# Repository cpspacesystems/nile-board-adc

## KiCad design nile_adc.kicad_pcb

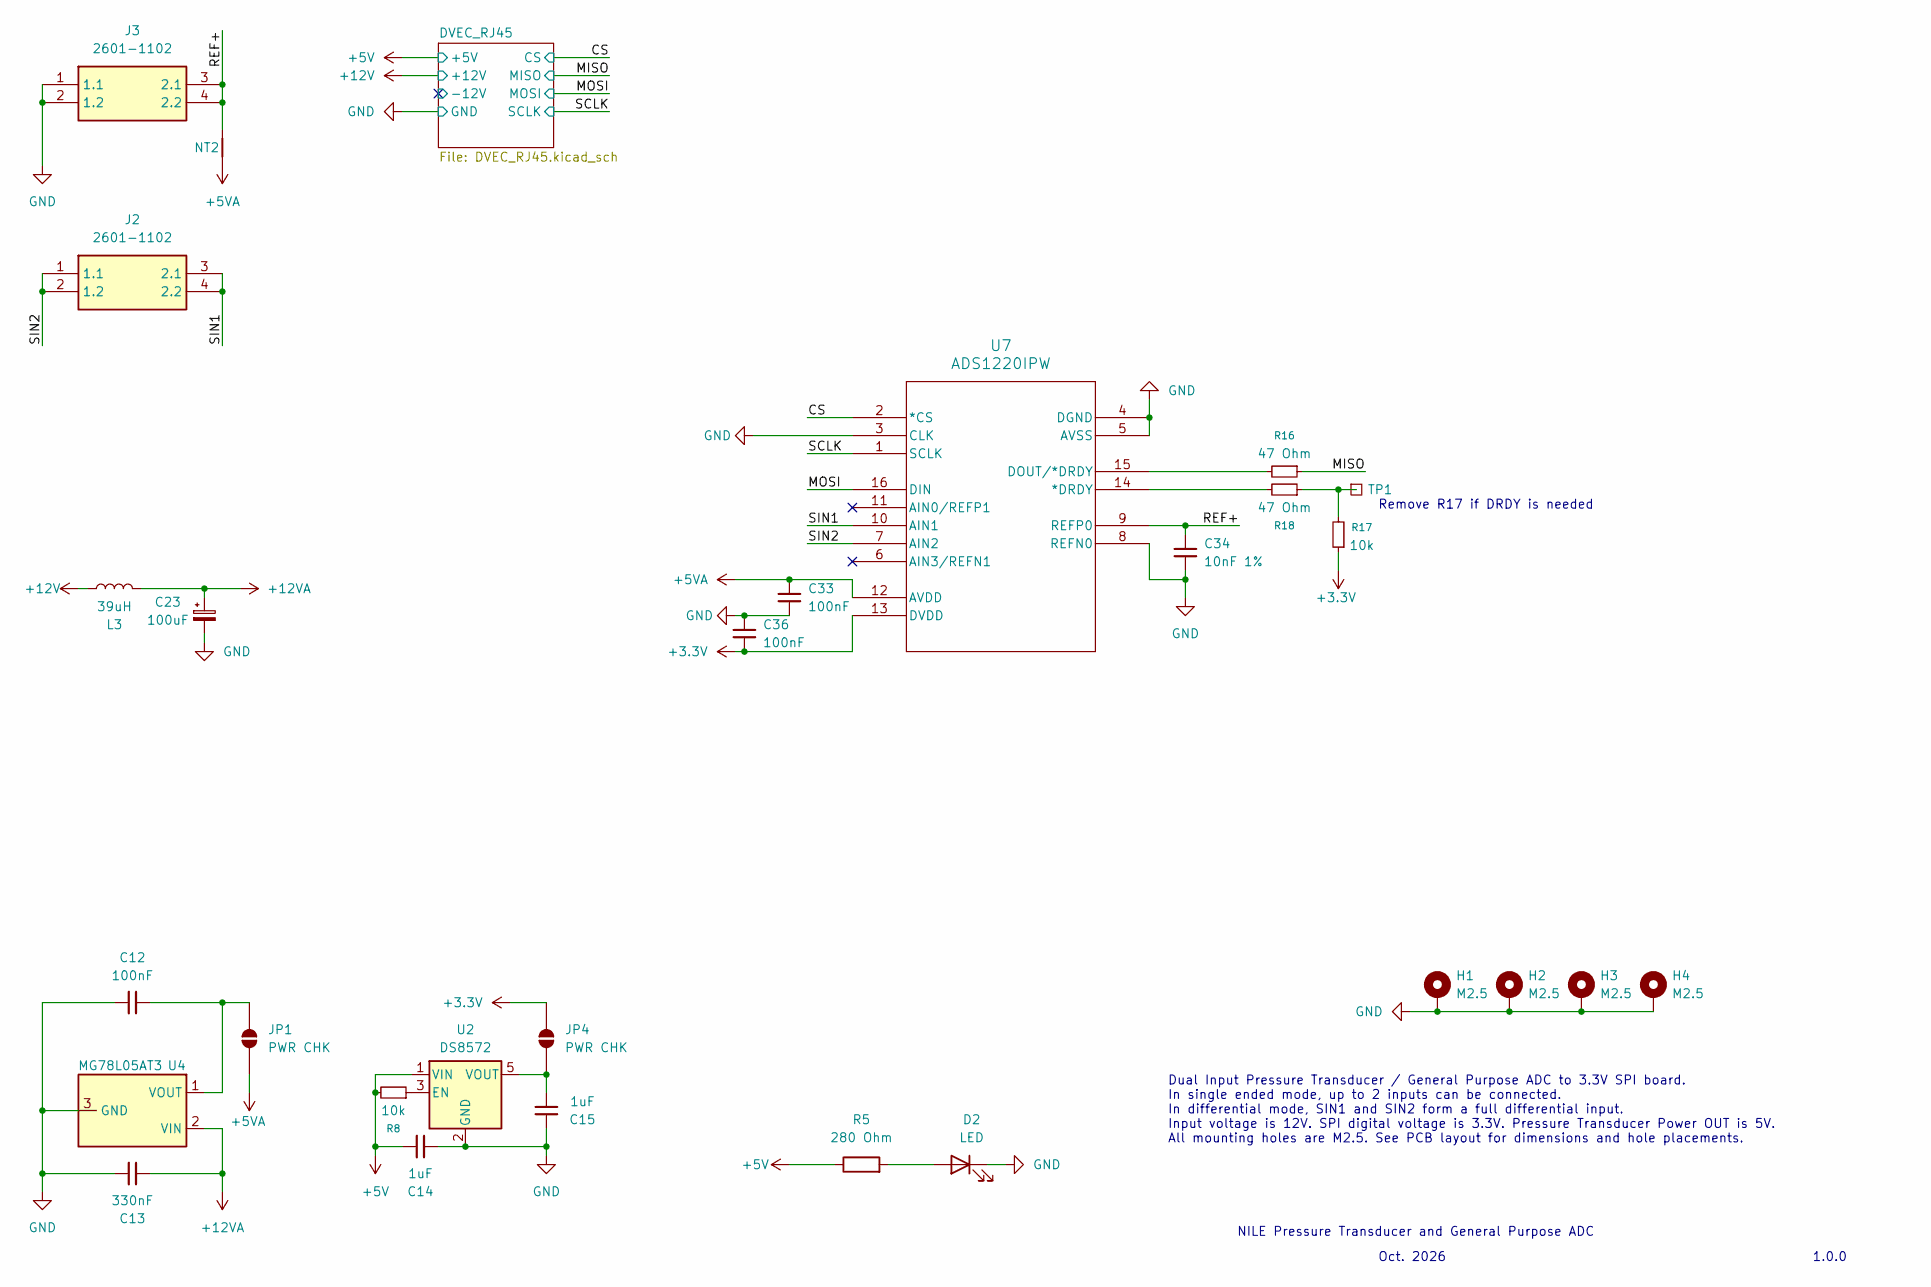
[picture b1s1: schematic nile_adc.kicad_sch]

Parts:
C12, C33, C36: 100nF; C_0402_1005Metric
C13: 330nF; C_0603_1608Metric
C14, C15: 1uF; C_0402_1005Metric
C23: 100uF; CP_Radial_D5.0mm_P2.00mm
C34: 10nF 1%; C_0603_1608Metric
D2: LED; LED_0603_1608Metric_Pad1.05x0.95mm_HandSolder
H1, H2, H3, H4: M2.5; MountingHole_2.5mm_Pad_TopBottom
J2, J3: 2601-1102; 26011102; Manufacturer_Part_Number 2601-1102
JP1, JP4: PWR CHK; C_0201_0603Metric
L3: 39uH; CMLF0504-390KTT
NT2: NetTie_2; NetTie-2_SMD_Pad0.5mm
R5: 280 Ohm; R_0402_1005Metric_Pad0.72x0.64mm_HandSolder
R8, R17: 10k; R_0402_1005Metric_Pad0.72x0.64mm_HandSolder
R16, R18: 47 Ohm; R_0402_1005Metric_Pad0.72x0.64mm_HandSolder
TP1: TestPoint_Square; TestPoint_Pad_2.5x2.5mm
U2: DS8572; SOT-23-5
U4: MG78L05AT3; SOT-23-3
U7: ADS1220IPW; PW16

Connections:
+3.3V: C36.2, JP4.1 (A), R17.1, U7.13 (DVDD)
+5V: C14.1, R5.1, R8.2, U2.1 (VIN); also elsewhere on the board
+5VA: C33.1, JP1.2 (B), NT2.1, U7.12 (AVDD)
+12V: L3.2; also elsewhere on the board
+12VA: C13.2, C23.1, L3.1, U4.2 (VIN)
/CS: U7.2 (*CS); also elsewhere on the board
/MISO: R16.1; also elsewhere on the board
/MOSI: U7.16 (DIN); also elsewhere on the board
/REF+: C34.1, J3.3 (2.1), J3.4 (2.2), NT2.2, U7.9 (REFP0)
/SCLK: U7.1 (SCLK); also elsewhere on the board
/SIN1: J2.3 (2.1), J2.4 (2.2), U7.10 (AIN1)
/SIN2: J2.1 (1.1), J2.2 (1.2), U7.7 (AIN2)
GND: C12.2, C13.1, C14.2, C15.1, C23.2, C33.2, C34.2, C36.1, D2.1 (K), H1.1 (1_1), H2.1 (1_1), H3.1 (1_1), H4.1 (1_1), J3.1 (1.1), J3.2 (1.2), U2.2 (GND), U4.3 (GND), U7.3 (CLK), U7.4 (DGND), U7.5 (AVSS), U7.8 (REFN0); also elsewhere on the board
unnamed: D2.2 (A), R5.2
unnamed: C12.1, JP1.1 (A), U4.1 (VOUT)
unnamed: C15.2, JP4.2 (B), U2.5 (VOUT)
unnamed: R17.2, R18.1, TP1.1 (1_1)
unnamed: R8.1, U2.3 (EN)
unnamed: R18.2, U7.14 (*DRDY)
unnamed: R16.2, U7.15 (DOUT/*DRDY)

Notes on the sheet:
1.0.0
Remove R17 if DRDY is needed
NILE Pressure Transducer and General Purpose ADC
Dual Input Pressure Transducer / General Purpose ADC to 3.3V SPI board. In single ended mode, up to 2 inputs can be connected. In differential mode, SIN1 and SIN2 form a full differential input. Input voltage is 12V. SPI digital voltage is 3.3V. Pressure Transducer Power OUT is 5V. All mounting hol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
Oct. 2026

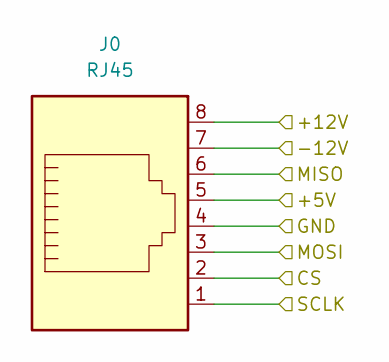
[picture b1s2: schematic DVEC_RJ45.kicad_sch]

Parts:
J0: RJ45; RJ45-TH_RJ-804-1-6 Yellow

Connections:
+5V: J0.5; also elsewhere on the board
+12V: J0.8; also elsewhere on the board
/CS: J0.2; also elsewhere on the board
/DVEC_RJ45/-12V: J0.7
/MISO: J0.6; also elsewhere on the board
/MOSI: J0.3; also elsewhere on the board
/SCLK: J0.1; also elsewhere on the board
GND: J0.4; also elsewhere on the board

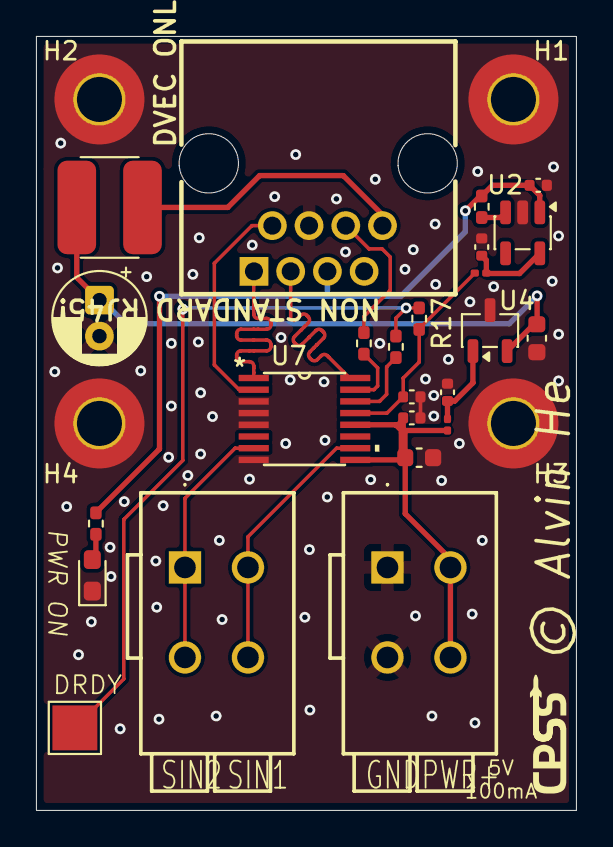
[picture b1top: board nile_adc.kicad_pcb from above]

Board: 2 copper layers, 30.0 x 43.0 mm, 29 parts (0 on the bottom side), 20 nets.

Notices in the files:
nile_adc.kicad_pcb:
© Alvin He
